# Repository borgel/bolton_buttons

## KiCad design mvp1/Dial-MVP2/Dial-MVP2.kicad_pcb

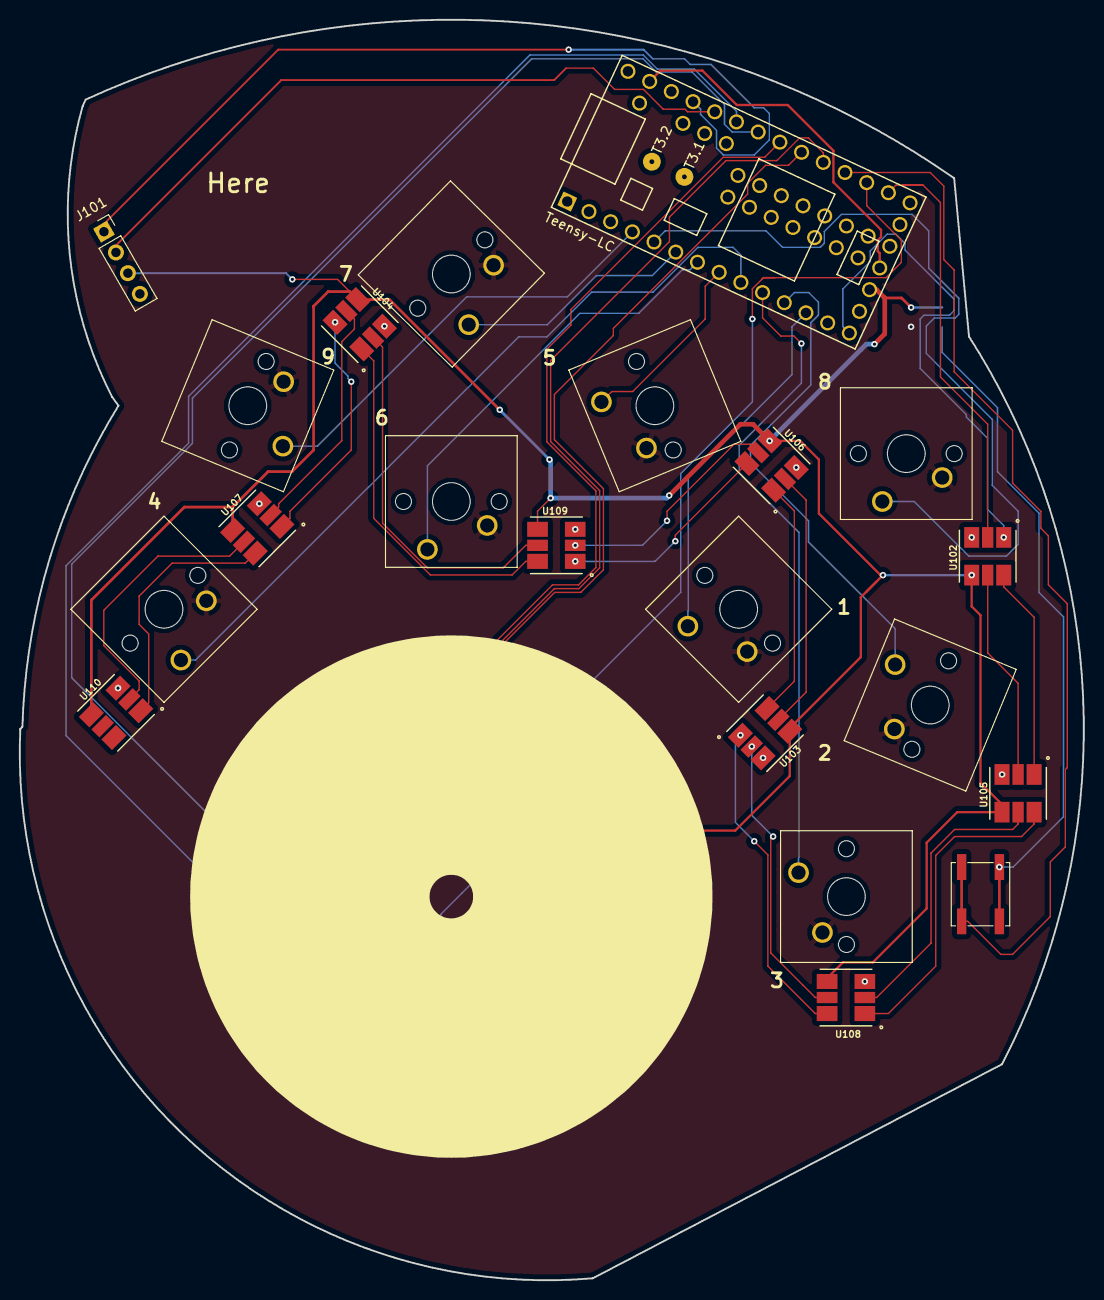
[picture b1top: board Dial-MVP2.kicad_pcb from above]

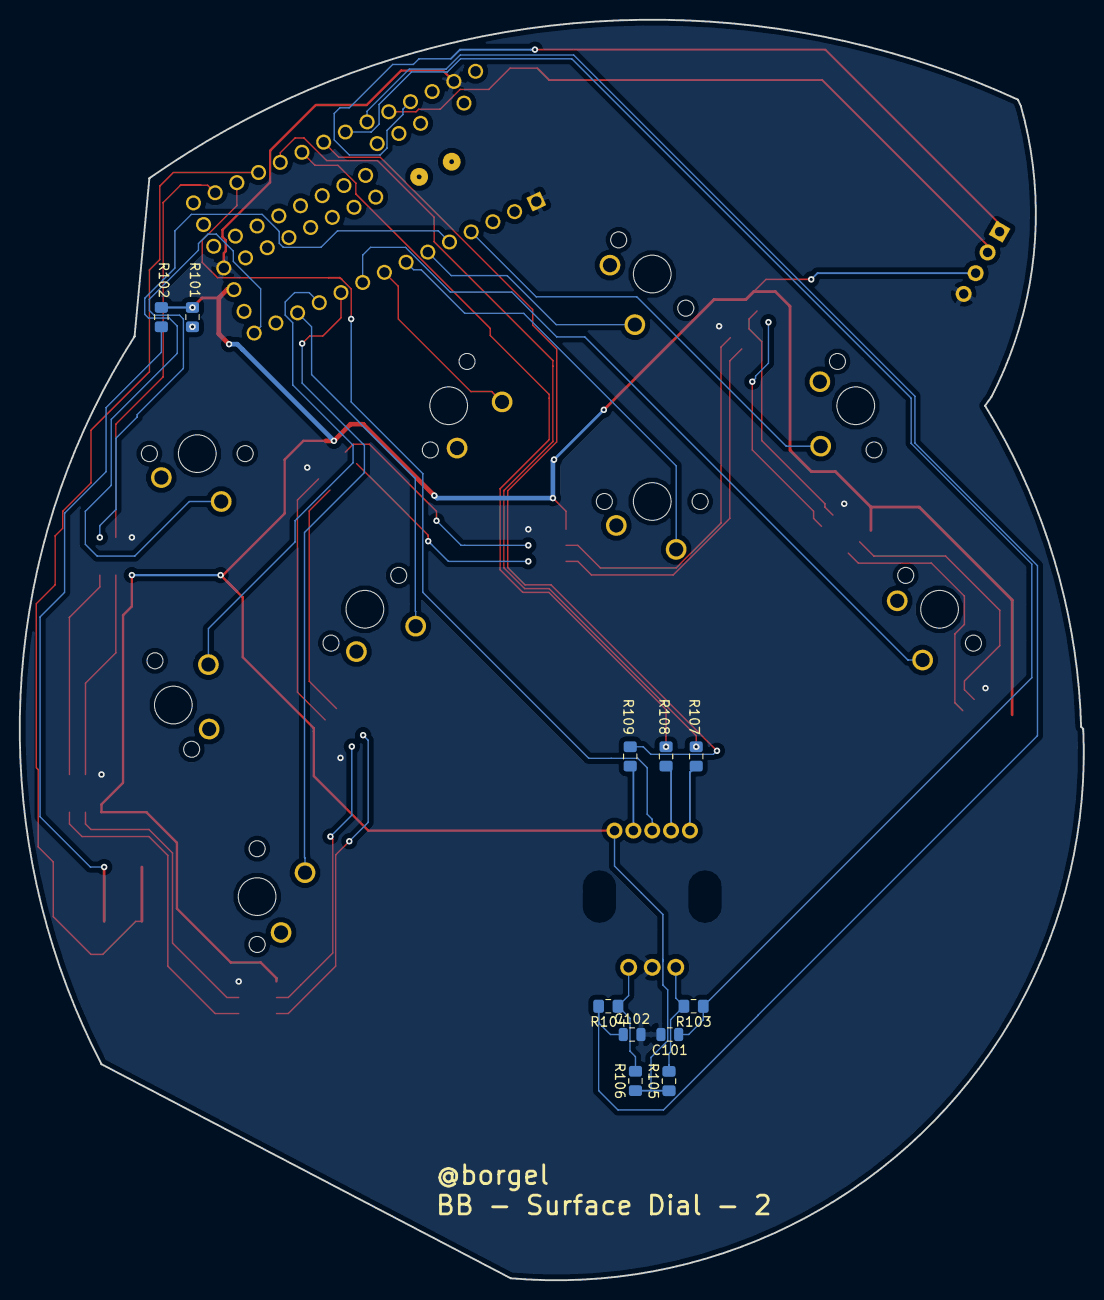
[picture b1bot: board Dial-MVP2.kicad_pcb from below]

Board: 2 copper layers, 112.9 x 133.7 mm, 33 parts (11 on the bottom side), 45 nets.

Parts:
C101, C102: 0.1uF; C_0805_2012Metric
J101: Conn_OLED; PinSocket_1x04_P2.54mm_Vertical
R101, R102, R103, R104, R105, R106: 10k; R_0805_2012Metric_Pad1.15x1.40mm_HandSolder
R107, R108, R109: 100r; R_0805_2012Metric_Pad1.15x1.40mm_HandSolder
SW101, SW102, SW103, SW104, SW105, SW106, SW107, SW108, SW109: SW_Push; SW_Cherry_MX1A_1.00u_PCB
SW110: SW_Push; SW_SPST_EVQP0
SW111: Rotary_Encoder_Switch_RGB; PEL12T-4xxxF-S1024
U101: Teensy-LC; Teensy30_31_32_LC
U102, U103, U104, U105, U106, U107, U108, U109, U110: APA102_5050; LED-5050

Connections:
+3V3: J101.3, R101.2, R102.1, R105.1, R106.1, SW111.5, U101.16, U102.4, U103.4, U104.4, U105.4, U106.4, U107.4, U108.4, U109.4, U110.4
/BTN_ALT_1: SW110.1, U101.23
/BTN_PU: R101.1, SW101.2, SW102.2, SW103.2, SW104.2, SW105.2, SW106.2, SW107.2, SW108.2, SW109.2
/BTN_SW: SW111.3, U101.22
/DISP_SCL: J101.2, U101.29
/DISP_SDA: J101.1, U101.30
/ENC_A: C101.1, R103.1, U101.27
/ENC_B: C102.1, R104.2, U101.28
/LEDS_MOSI: U101.14, U102.1
/LEDS_SCK: U101.21, U102.2
/LED_B: R109.2, U101.26
/LED_G: R108.2, U101.25
/LED_R: R107.2, U101.24
GND: C101.2, C102.2, J101.4, SW111.C, U101.1, U101.17, U101.32, U102.3, U103.3, U104.3, U105.3, U106.3, U107.3, U108.3, U109.3, U110.3
unnamed: R102.2, SW110.2
unnamed: R103.2, R105.2, SW111.A
unnamed: R104.1, R106.2, SW111.B
unnamed: R107.1, SW111.1
unnamed: R108.1, SW111.2
unnamed: R109.1, SW111.4
unnamed: SW101.1, U101.12
unnamed: SW102.1, U101.11
unnamed: SW103.1, U101.10
unnamed: SW104.1, U101.9
unnamed: SW105.1, U101.8
unnamed: SW106.1, U101.7
unnamed: SW107.1, U101.6
unnamed: SW108.1, U101.5
unnamed: SW109.1, U101.4
unnamed: U102.5, U105.2
unnamed: U102.6, U105.1
unnamed: U103.1, U108.6
unnamed: U103.2, U108.5
unnamed: U103.5, U106.2
unnamed: U103.6, U106.1
unnamed: U104.1, U109.6
unnamed: U104.2, U109.5
unnamed: U104.5, U107.2
unnamed: U104.6, U107.1
unnamed: U105.5, U108.2
unnamed: U105.6, U108.1
unnamed: U106.5, U109.2
unnamed: U106.6, U109.1
unnamed: U107.5, U110.2
unnamed: U107.6, U110.1

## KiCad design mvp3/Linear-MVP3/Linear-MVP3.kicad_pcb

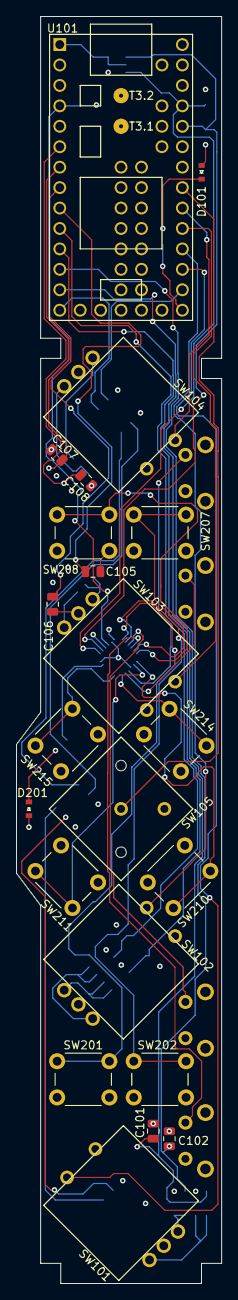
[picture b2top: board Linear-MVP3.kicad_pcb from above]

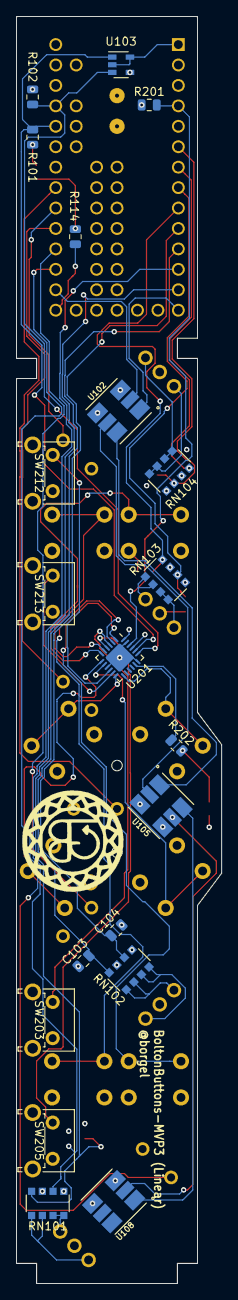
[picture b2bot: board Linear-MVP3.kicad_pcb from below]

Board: 4 copper layers, 25.5 x 157.5 mm, 42 parts (20 on the bottom side), 48 nets.

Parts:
C101, C102, C103, C104, C105, C106, C107, C108: 0.1uF; C_0805_2012Metric
D101, D201: LED_ALT; LED_0603_SmallSilk
R101, R102: 4.7k; R_0805_2012Metric
R114, R202: 500r; R_0805_2012Metric
R201: 10k; R_0805_2012Metric
RN101, RN102, RN103, RN104: R_Pack 10k; R_Array_Convex_4x1206
SW101, SW102, SW103, SW104: Rotary_Encoder_Switch; PEC11R
SW105: SW_Push; Schurter-MTG
SW201, SW202, SW207, SW208, SW210, SW211, SW214, SW215: SW_Push; SW_PUSH_6mm
SW203, SW205, SW212, SW213: SW_Push; SW_Tactile_SPST_Angled_PTS645Vx83-2LFS
U101: Teensy-LC; Teensy30_31_32_LC
U102, U105, U108: APA102_5050; LED-5050
U103: 24LC16-SOT-23-5; SOT-23-5
U201: TCA9555RTWR; QFN-24-1EP_4x4mm_P0.5mm_EP2.6x2.6mm

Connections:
+3V3: D101.2, D201.2, R101.1, R102.1, R201.1, RN101.5, RN101.7, RN102.5, RN102.7, RN103.5, RN103.7, RN104.5, RN104.7, U101.31, U102.4, U103.4, U105.4, U108.4, U201.21, U201.24
/BTN_BIG_MID: SW105.1, U101.26
/BTN_INT: R201.2, U101.4, U201.22
/Buttons/BTN_PAIR_1_A: SW201.1, U201.1
/Buttons/BTN_PAIR_1_B: SW202.1, U201.2
/Buttons/BTN_PAIR_2_SIDE: SW203.1, U201.3
/Buttons/BTN_PAIR_2_TOP: SW205.1, U201.4
/Buttons/BTN_PAIR_3_A: SW207.1, U201.5
/Buttons/BTN_PAIR_3_B: SW208.1, U201.6
/Buttons/BTN_PAIR_4_A: SW210.1, U201.7
/Buttons/BTN_PAIR_4_B: SW211.1, U201.8
/Buttons/BTN_PAIR_5_SIDE: SW212.1, U201.10
/Buttons/BTN_PAIR_5_TOP: SW213.1, U201.11
/Buttons/BTN_PAIR_6_A: SW214.1, U201.12
/Buttons/BTN_PAIR_6_B: SW215.1, U201.13
/Buttons/LED_STATUS: R202.2, U201.17
/ENC_1_A: C101.1, RN101.8, U101.13
/ENC_1_B: C102.1, RN101.6, U101.12
/ENC_1_SW: SW101.S1, U101.22
/ENC_2_A: C103.1, RN102.8, U101.11
/ENC_2_B: C104.1, RN102.6, U101.10
/ENC_2_SW: SW102.S1, U101.23
/ENC_3_A: C105.1, RN103.8, U101.9
/ENC_3_B: C106.1, RN103.6, U101.8
/ENC_3_SW: SW103.S1, U101.24
/ENC_4_A: C107.1, RN104.8, U101.7
/ENC_4_B: C108.1, RN104.6, U101.6
/ENC_4_SW: SW104.S1, U101.25
/I2C1_SCL: R101.2, U101.29, U103.1, U201.20
/I2C1_SDA: R102.2, U101.30, U103.3, U201.19
/LEDS_MOSI: U101.14, U102.1
/LEDS_SCK: U101.21, U102.2
/LED_ALIVE: R114.2, U101.20
GND: C101.2, C102.2, C103.2, C104.2, C105.2, C106.2, C107.2, C108.2, SW101.C, SW101.S2, SW102.C, SW102.S2, SW103.C, SW103.S2, SW104.C, SW104.S2, SW105.2, SW201.2, SW202.2, SW203.2, SW205.2, SW207.2, SW208.2, SW210.2, SW211.2, SW212.2, SW213.2, SW214.2, SW215.2, U101.1, U101.17, U101.32, U102.3, U103.2, U103.5, U105.3, U108.3, U201.9, U201.18, U201.23, U201.25
unnamed: D101.1, R114.1
unnamed: D201.1, R202.1
unnamed: RN101.1, RN101.2, SW101.A
unnamed: RN101.3, RN101.4, SW101.B
unnamed: RN102.1, RN102.2, SW102.A
unnamed: RN102.3, RN102.4, SW102.B
unnamed: RN103.1, RN103.2, SW103.A
unnamed: RN103.3, RN103.4, SW103.B
unnamed: RN104.1, RN104.2, SW104.A
unnamed: RN104.3, RN104.4, SW104.B
unnamed: U102.5, U105.2
unnamed: U102.6, U105.1
unnamed: U105.5, U108.2
unnamed: U105.6, U108.1

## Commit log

2018-12-04 Arduino Stub
2018-12-04 USB Keyboard test
2018-12-04 Begin button array to config process
2018-12-06 Get LEDs working
2018-12-06 Add basic button reading and debounce
2018-12-06 Broken display test code
2018-12-06 Display works!
2018-12-06 Update button map to label what is what
2018-12-06 Show what's pressed on the display
2018-12-06 Send the right keys when pressed
2018-12-06 Simplify keyboard
    https://www.pjrc.com/teensy/td_keyboard.html
2018-12-06 Light the LED for the pressed key
2018-12-08 Start factoring keypresses into a single callback
2018-12-08 Factor keymap out from physical buttons
2018-12-08 Clean out dead code
2018-12-08 Support multiple keymaps and switch between them
2018-12-08 Increase debounce interval
2018-12-08 Start real keymap for layout and testing
2018-12-08 Add modifier support
2018-12-08 Try writing out all key mappings to screen
2018-12-10 Add encoder support
2018-12-10 Add test code for the rotary encoder
2018-12-10 Clean up knob, add handy fxns
2018-12-10 Turn on knob when a key is pressed
2018-12-10 Start support for dial modifiers
2018-12-11 Simplify key press logic
2018-12-11 Preliminary knob support
2018-12-11 Clean up dead code in main
2018-12-11 Const more of keymaps
2018-12-11 Add layout keymap
2018-12-11 Show what knob is bound to when a key is pressed
2018-12-11 Control arrow keys with knob by default
2018-12-12 Show key name when showing alt fxns
2018-12-12 Disable light on key
2018-12-12 Add basic viewport control
2018-12-12 Release each key's pressed state on knob
2018-12-12 Adjust viewport controls
2018-12-12 Add layout-based default dial behaviors
2019-03-05 Starting MVP3 src from MVP1
2019-03-06 Add stock lib for TCA9555 expander
2019-03-06 Hardware TCA lib to work with Teensy LC
2019-03-06 Start test sketch that can speak to IO expander to write
2019-03-06 Fix TCA lib not properly requesting reads
2019-03-06 More lib cleanup
2019-03-06 Configure and read some buttons via IO expander
2019-03-06 Read all buttons via expander
2019-03-06 Fire an interrupt on button press
2019-03-06 Test knobs
2019-03-06 Add LED strip test code
2019-03-06 Strip display stuff from code
2019-03-07 Add modified IO expander driver
2019-03-07 Start SmartKnob
2019-03-07 Strip more old code, start using SmartKnobs
2019-03-07 Wire encoder buttons through keyboard code
2019-03-07 Temporarily disable sending keyboard keys
2019-03-07 Track all knobs for changes
2019-03-07 Calculate and track knob change
2019-03-07 Add big center direct button
2019-03-07 Add a divisor to knob changes/counts
2019-03-07 Fire knob events on change
2019-03-07 Add a module to track changes on the IO expander and fire a CB for them
2019-03-07 Integrate IO expander buttons into main loop
2019-03-08 Rework keymaps, enable all buttons and knobs thru maps
2019-03-08 Make middle button press esc
2019-03-08 Label buttons in logical map
2019-03-08 First draft layout
2019-03-08 Enable keyboard press
2019-03-08 Swap pairs around middle button
2019-04-27 Add hardware files for V2 (listed as v1 here) and V3
